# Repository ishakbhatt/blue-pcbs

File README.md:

# BLUE | Biannual Launches for Undergraduate Engineers

1. ADC/DAC to RPi: This board was initially for a small Payload, but I found an off-the-shelf equivalent compatible with the RPi form factor. Although customizing this board became pretty much obsolete, it will certainly help to refer back to my version if we ever need a chip with more external ADC/DAC interfacing. More than anything, this just became my practice board for getting through the entire board design process.

2. Motor Controller Board: faced a lot of issues with some off-the-shelf motor controller options including frying one of the RPis, so we decided to make our own with necessary protection including 2 flyback diodes, a zener diode shunted to ground, and potential decoupling capacitors.

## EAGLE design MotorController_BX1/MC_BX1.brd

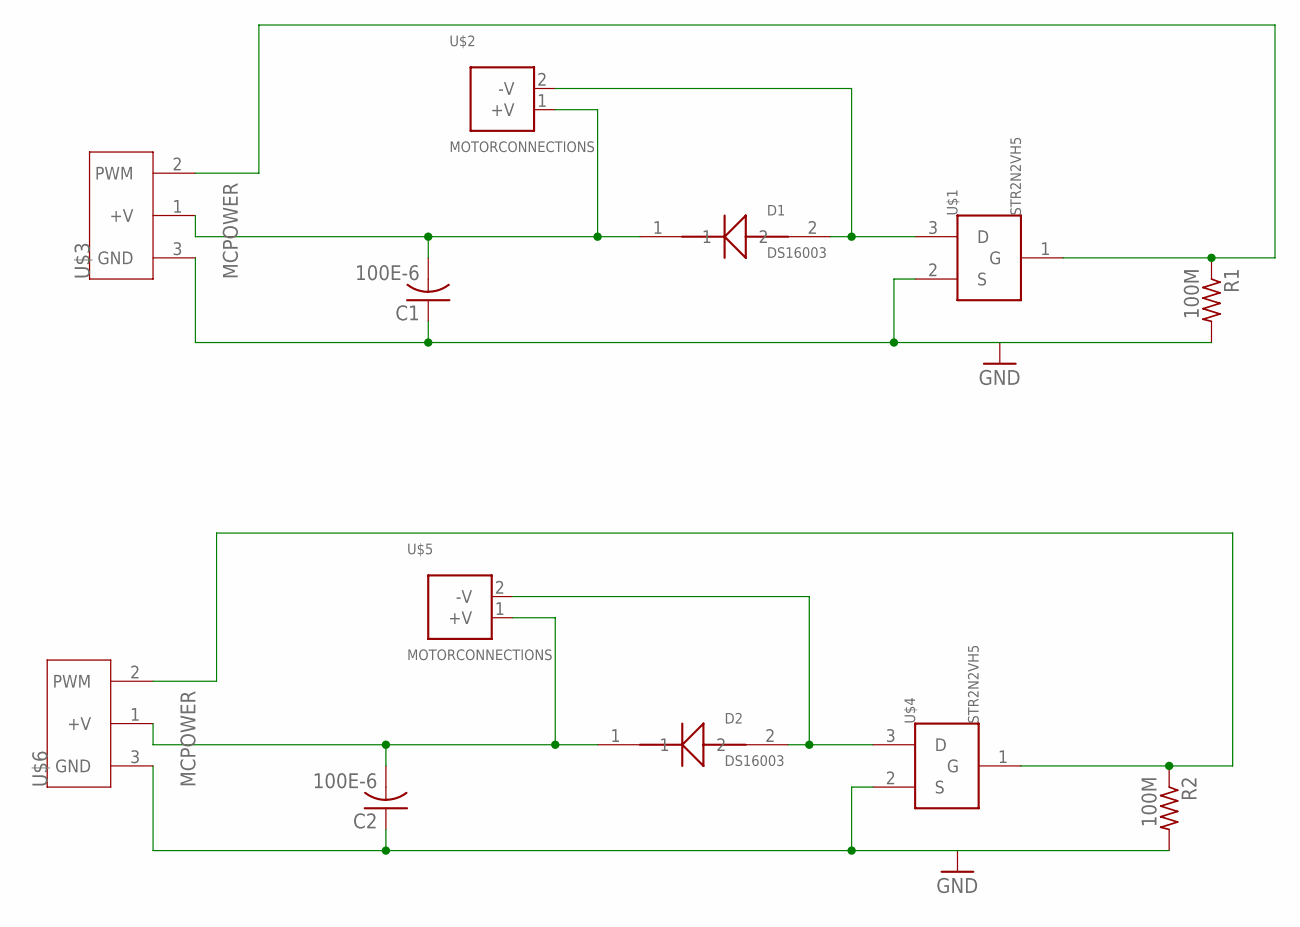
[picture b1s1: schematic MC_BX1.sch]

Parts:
C1, C2: 100E-6; C0805
D1, D2: DS16003; DS16003_F
R1, R2: 100M; R0805
U$1, U$4: STR2N2VH5; T-STR2N2VH5_F
U$2, U$5: MOTORCONNECTIONS
U$3, U$6: MCPOWER

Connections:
GND: C1.1, C2.1, R1.2, R2.2, U$1.2 (S), U$3.3 (GND), U$4.2 (S), U$6.3 (GND)
unnamed: D1.2, U$1.3 (D), U$2.2 (-V)
unnamed: D2.2, U$4.3 (D), U$5.2 (-V)
unnamed: R1.1, U$1.1 (G), U$3.2 (PWM)
unnamed: R2.1, U$4.1 (G), U$6.2 (PWM)
unnamed: C2.2, D2.1, U$5.1 (+V), U$6.1 (+V)
unnamed: C1.2, D1.1, U$2.1 (+V), U$3.1 (+V)

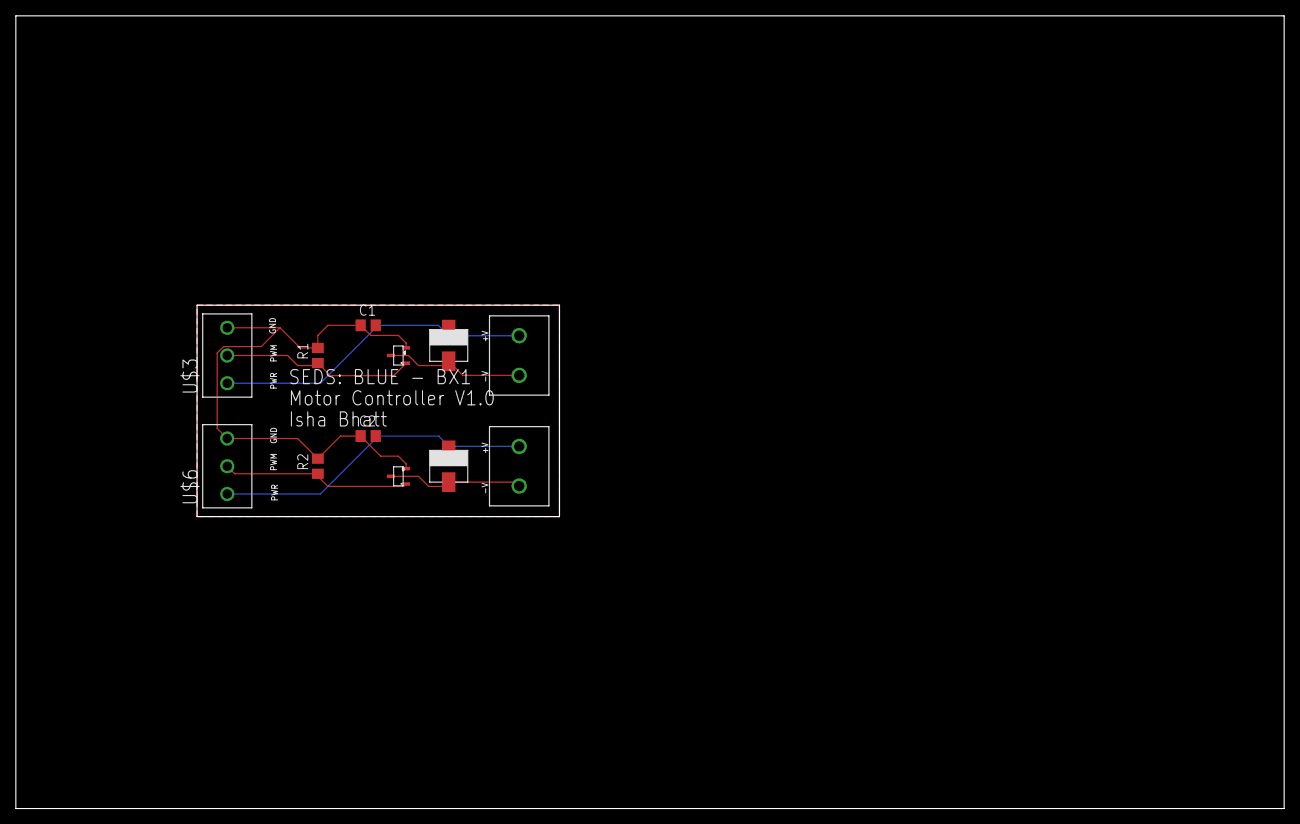
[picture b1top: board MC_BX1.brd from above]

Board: 2 copper layers, 160.0 x 100.0 mm, 12 parts (0 on the bottom side), 7 nets.

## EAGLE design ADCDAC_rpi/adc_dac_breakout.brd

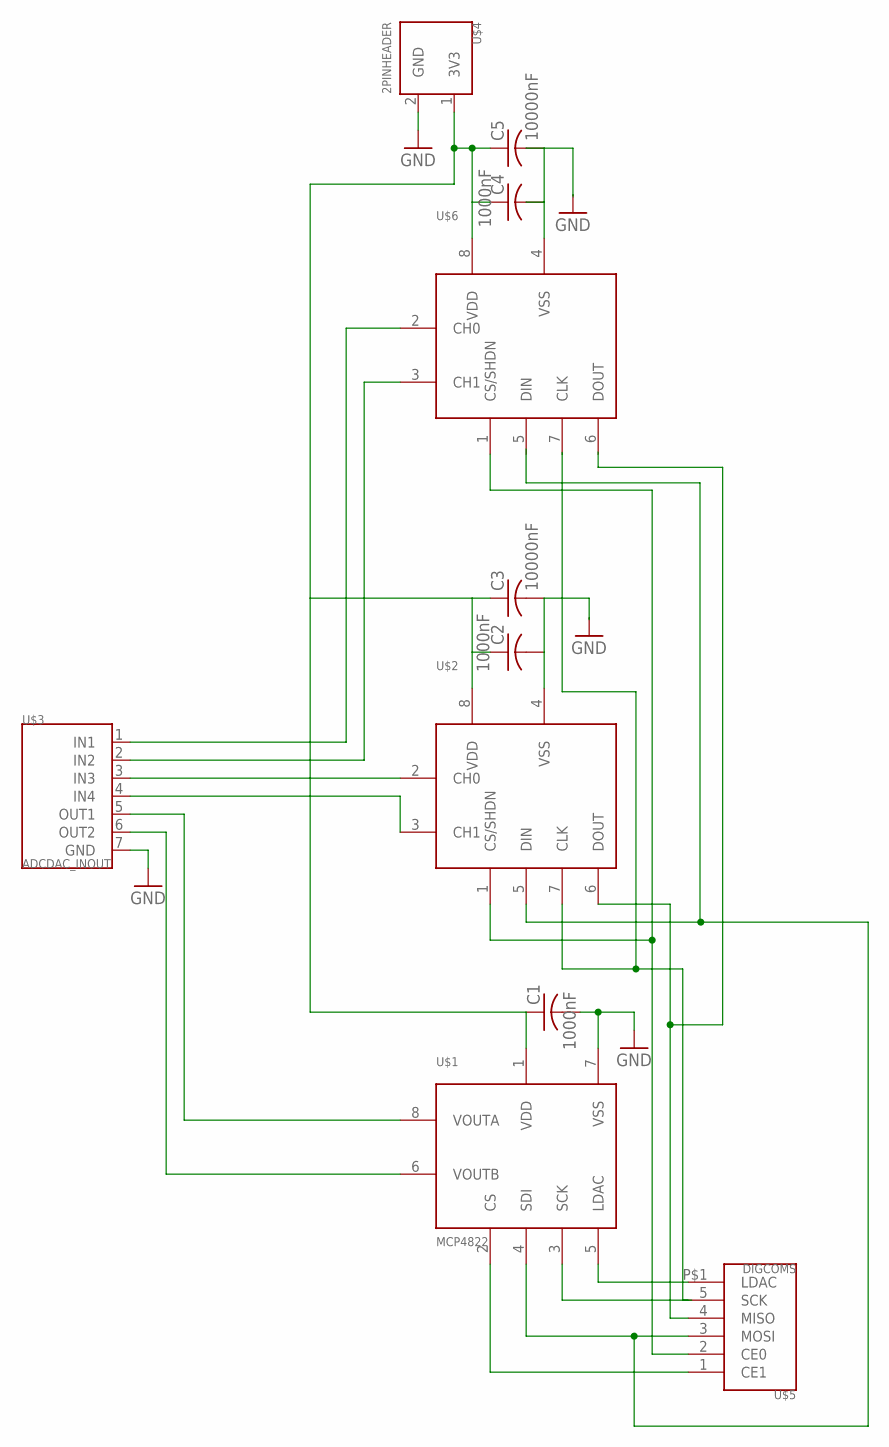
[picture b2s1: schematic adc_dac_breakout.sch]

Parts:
C1, C2, C4: 1000nF; C0603
C3, C5: 10000nF; C0603
U$1: MCP4822
U$2, U$6: MCP3202
U$3: ADCDAC_INOUT; 7PINHEADER
U$4: 2PINHEADER
U$5: DIGCOMS; 6PINHEADER

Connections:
GND: C1.2, U$1.7 (VSS), U$3.7 (GND), U$4.2 (GND)
unnamed: U$1.2 (CS), U$5.1 (CE1)
unnamed: U$1.8 (VOUTA), U$3.5 (OUT1)
unnamed: U$1.6 (VOUTB), U$3.6 (OUT2)
unnamed: U$1.4 (SDI), U$2.5 (DIN), U$5.3 (MOSI)
unnamed: U$1.3 (SCK), U$5.5 (SCK)
unnamed: U$1.5 (LDAC), U$5.P$1 (LDAC)
unnamed: U$2.1 (CS/SHDN), U$5.2 (CE0), U$6.1 (CS/SHDN)
unnamed: C2.2, C3.2, U$2.4 (VSS)
unnamed: U$2.3 (CH1), U$3.4 (IN4)
unnamed: C4.2, C5.2, U$6.4 (VSS)
unnamed: U$2.2 (CH0), U$3.3 (IN3)
unnamed: U$3.2 (IN2), U$6.3 (CH1)
unnamed: U$3.1 (IN1), U$6.2 (CH0)
unnamed: U$2.6 (DOUT), U$5.4 (MISO)
unnamed: U$2.7 (CLK), U$6.7 (CLK)
unnamed: C1.1, C2.1, C3.1, C4.1, C5.1, U$1.1 (VDD), U$2.8 (VDD), U$4.1 (3V3), U$6.8 (VDD)

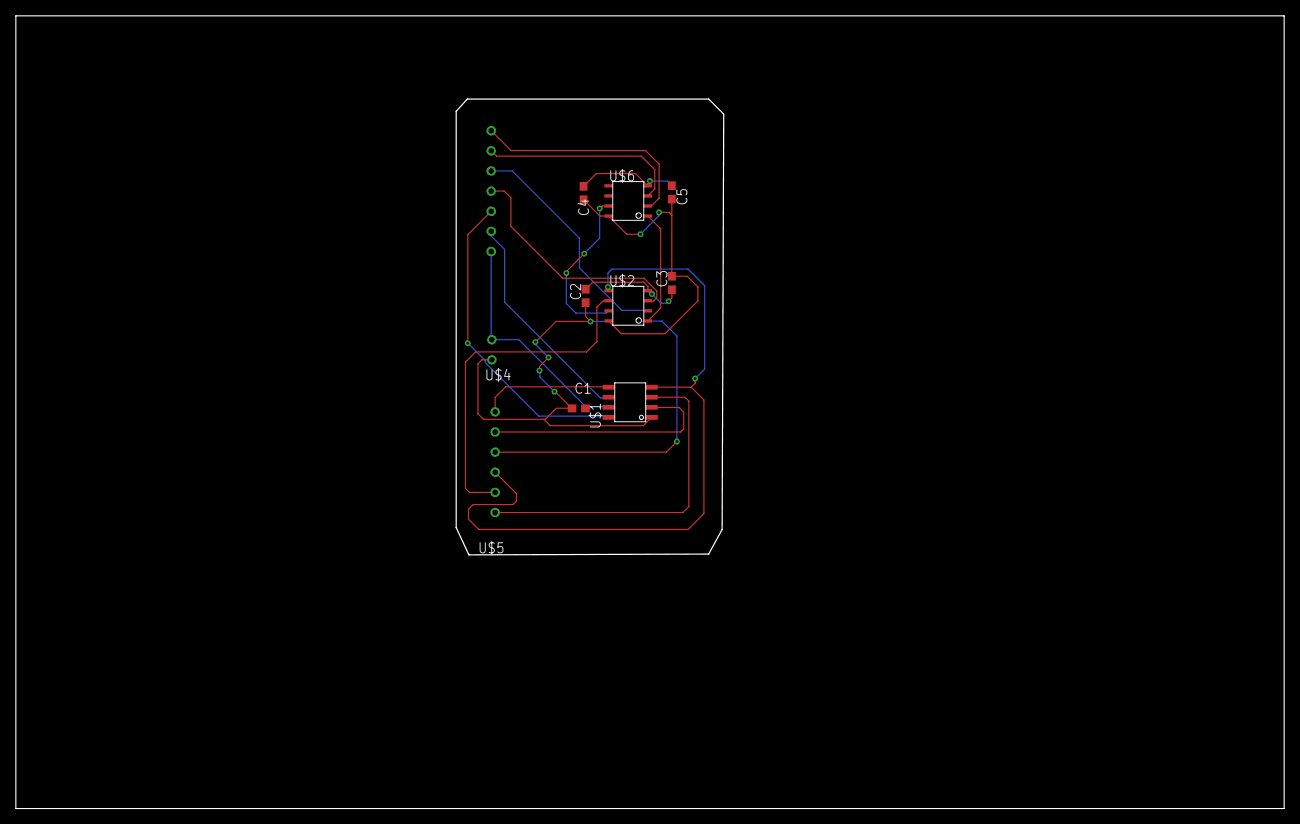
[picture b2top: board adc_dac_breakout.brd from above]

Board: 2 copper layers, 160.0 x 100.0 mm, 11 parts (0 on the bottom side), 17 nets.

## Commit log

2019-08-03 adding ADC/DAC Breakout Practice Project
2019-08-03 adding SEDS library + libraries directory
2019-08-03 motor controller in progress... adding preliminary schematic here
2019-08-05 Finished first revision of motor controller schematic. Pending: zener shunted to ground, C1 value, and decoupling capacitors from PWM to GND
2019-08-05 modified symbols for easy wiring in schematic
2019-08-06 finished board design for BX1 motor controller
